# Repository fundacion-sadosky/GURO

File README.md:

🌐 [English](README.en.md)

# GURO

**Kit de conversión para robots Robobloq Qoopers con [BBC Micro:bit](https://www.microbit.org)**

La Fundación Sadosky desarrolla el kit GURO para actualizar los robots Robobloq Qoopers —ya desplegados en escuelas de todo el país— reemplazando el controlador propietario Qmind Plus por la [BBC Micro:bit](https://www.microbit.org): una placa didáctica de hardware y software completamente abiertos, con una comunidad global activa de millones de docentes y estudiantes.

---

## ¿Qué es el kit GURO?

El kit GURO consiste en una **placa adaptadora** (diseño KiCad incluido en este repositorio) y un **gabinete** que permiten montar una BBC Micro:bit y una placa expansora [Kittenbot Robotbit](https://kittenbothk-eng.readthedocs.io/en/latest/Microbit_eboard/Robotbit/robotbitMC.html) en el chasis del Robobloq Qoopers, conectando los motores y sensores existentes del robot.

El resultado es un robot funcional, programable desde el navegador en bloques visuales o en Python, sin depender de ningún software propietario ni de un único proveedor.

El modelos 3D del robot y el gabinete están disponibles en este repositorio y en [Tinkercad](https://www.tinkercad.com/things/2tzfirybpMV-guro-microrbit-para-robolboq-qoopers-260401)

---

## Requisitos

- **Kit Robobloq Qoopers** — chasis, motores, sensores y partes mecánicas (sin el Qmind Plus)
- **Kit GURO** — placa adaptadora y gabinete Micro:bit (este repositorio)
- **[BBC Micro:bit](https://www.microbit.org)** v1 o v2
- Un destornillador Phillips
- Una computadora con puerto USB

---

## Guía de armado

La documentación completa está publicada en:

**[guro.readthedocs.io](https://guro.readthedocs.io/)**

Incluye el inventario de piezas, 16 pasos ilustrados y las instrucciones de programación. También disponible [en PDF](docs/user-guide_2026-04-01.pdf)

---

## Programación del robot

Una vez armado el GURO, cargá un programa a la Micro:bit desde el navegador, sin instalar nada:

### Opción 1 — Bloques visuales (MakeCode)

Usá el editor [Microsoft MakeCode](https://makecode.microbit.org) con la extensión **Kittenbot Robotbit** para programar el robot con bloques. [Ver instrucciones de la extensión.](https://kittenbothk-eng.readthedocs.io/en/latest/Microbit_eboard/Robotbit/robotbitMC.html)

### Opción 2 — Python

Usá el [editor oficial de MicroPython](https://python.microbit.org/v/3) de la [Micro:bit Educational Foundation](https://github.com/microbit-foundation).

El framework [**microbitML**](https://github.com/fundacion-sadosky/microbitML) (Fundación Sadosky) incluye la actividad `mbGURO`, lista para comandar al robot. Podés descargar el archivo `.hex` y bajarlo directamente a la placa.

---

## Estructura del repositorio

```
docs/               Documentación del sitio (properDocs + Obsidian)
kit GURO/           Inventario del kit 
gabinete/           Gabinete para Micro:bit y placa expansora
placa adaptadora/   Diseño de la placa PCB adaptadora (KiCad)
scripts/            Scripts de generación de documentación (properDocs/MkDocs)
mkdocs.yml          Configuración del sitio de documentación 
docs-requirements.txt  Dependencias Python para compilar la documentación 
```

La carpeta `docs/` está configurada como un vault de [Obsidian](https://obsidian.md), lo que permite editarla sin usar la terminal. Ver [Contribuciones para redactores](https://guro.readthedocs.io/contributing/for-writers/).

---

## Oportunidades de colaboración

Estas son algunas tareas concretas en las que podés contribuir al proyecto:

1. **Avistaje**: si lo usan en tu escuela, compartí la experiencia B)
1. **Completar la Mecánica**: pasar el diseño 3D del gabinete de [Tinkercad](https://www.tinkercad.com/things/2tzfirybpMV-guro-microrbit-para-robolboq-qoopers-260401) a un formato mantenible/paramétrico como openScad.
1. **Completar la Mecánica**: el capó no encaja en la tapa del gabinete.
1. **Completar la Mecánica**: la tapa del gabinete choca con el porta batería del Kittenbot.
1. **Completar la Guía**: los pasos 13, 14 y 16 de la guía de armado no tienen imágenes aún. Si tenés un kit armado, podés tomar las fotos y abrir un PR.
1. **Traducir la documentación al Inglés**: la guía de armado y el README están disponibles solo en español. Traducirlos ampliaría el alcance del proyecto a la comunidad internacional de Micro:bit.
1. **Crear una extensión de MakeCode específica para GURO**: actualmente se usa la extensión genérica de Kittenbot Robotbit. Una extensión propia simplificaría la programación en bloques con nombres y funciones adaptados al GURO.

## Contribuciones

Las contribuciones son bienvenidas, independientemente del perfil técnico.

- **Redactores y docentes**: editá la documentación con [Obsidian](https://obsidian.md) abriendo la carpeta `docs/` como vault. Ver [guía para redactores](https://guro.readthedocs.io/contributing/for-writers/).
- **Desarrolladores**: mirá la [guía para desarrolladores](https://guro.readthedocs.io/contributing/for-developers/).
- **Errores o sugerencias**: abrí un [issue](../../issues) en este repositorio.

---

## Créditos

Colaboradores/as iniciales, por orden alfabético:

| Nombre   | Rol                         |
|---------------------------|-----------------------------|
| Alarcón Lasagno, Ramiro   | Doc, SW, HW                 | 
| Batlle, Leandro           | Doc, SW , HW, idea original |
| Gentile Montes, Ezequiel  | Mecánica                    |
| Medel, Ricardo            | Licencias Doc, FLOSS, OSHW  |

*¿Contribuiste al proyecto? Abrí un PR para agregar tu nombre y aportes.*

Este proyecto utiliza la [BBC Micro:bit](https://www.microbit.org), desarrollada por la [Micro:bit Educational Foundation](https://github.com/microbit-foundation). La Micro:bit Foundation publica sus especificaciones de hardware, firmware y recursos educativos bajo licencias abiertas en [github.com/microbit-foundation](https://github.com/microbit-foundation).

---

## Marcas registradas

Los nombres de productos y marcas mencionados en este repositorio (incluyendo BBC Micro:bit, Robobloq, Qoopers, Kittenbot, Robotbit, Microsoft MakeCode, entre otros) son propiedad de sus respectivos titulares y se utilizan únicamente con fines identificativos y descriptivos.

## Naturaleza del proyecto

El desarrollo comenzó en la Fundación Sadosky en el marco del Programa para el Desarrollo de la Infraestructura destinada a Promover la Capacidad Emprendedora financiado por la [CAF | Banco de desarrollo de América Latina y El Caribe](https://www.caf.com/).  GURO es un kit de conversión que permite reutilizar las partes mecánicas, motores y sensores del Robobloq Qoopers con una nueva  placa controladora. El proyecto no modifica ni redistribuye el firmware, software ni diseños de hardware de los productos de terceros que integra. 

## Garantías y responsabilidad

Este proyecto se distribuye sin garantía de ningún tipo, expresa o  implícita. El armado, uso y eventual modificación del kit son responsabilidad exclusiva del usuario. Consultá las licencias GPLv3 y CC BY-SA 4.0 incluidas en este repositorio para los términos  completos. El uso del kit en entornos educativos debe realizarse bajo supervisión docente y conforme a las normativas de seguridad aplicables en cada jurisdicción. 

## Licencias

El proyecto se distribuye bajo una **licencia dual**:

### Código y diseños de hardware
Publicado bajo la [**GNU General Public License v3.0**](LICENSE) (GPLv3).
Podés usar, modificar y redistribuir el código y los diseños KiCad, siempre que cualquier obra derivada se publique bajo la misma licencia.

### Documentación
Publicada bajo [**Creative Commons Atribución-CompartirIgual 4.0 Internacional**](https://creativecommons.org/licenses/by-sa/4.0/) (CC BY-SA 4.0).
Podés copiar, adaptar y redistribuir el contenido —incluso con fines comerciales— siempre que des crédito a los autores originales y distribuyas las obras derivadas bajo la misma licencia.

---

<p align="center">
  <a href="https://www.fundacionsadosky.org.ar">Fundación Sadosky</a>
</p>

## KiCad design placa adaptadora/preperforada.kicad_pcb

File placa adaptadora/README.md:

🌐 [English](README.en.md)

# Placa Adaptadora — Kit GURO

Diseño [KiCad](https://www.kicad.org/) de la **placa adaptadora**, componente del [kit GURO](../kit%20GURO/README.md).

---

## ¿Qué hace esta placa?

La placa adaptadora es el puente eléctrico central del kit GURO.
Conecta todos los periféricos del chasis Qoopers a la [Kittenbot Robotbit](https://kittenbothk-eng.readthedocs.io/en/latest/Microbit_eboard/Robotbit/robotbitMC.html):

```
Kittenbot Robotbit
      │
      ├── Motores (×2) — conectores de 6 pines
      ├── Sensores  ─┐
      ├── GPIO       ├── conectores RJ25 (6 Posiciones / 6 Contactos)
      └── Panel LED ─┘
```

También incorpora la conexión a la **placa de alimentación** del kit, PRECAUCIÓN:

> [!WARNING]
> NUNCA conectar la batería del Robobloq Qoopers directamente al Kittenbot Robotbit: es necesario regular su tensión a 5V (con 15W), que es la función de la "placa de alimentación".

---

## Vista del diseño PCB

El diseño está optimizado para ser **intercambiable con una [placa universal de 50×70 mm](https://www.printables.com/model/797008-perfboard-50x70mm-18-x-24-holes)**, lo que permite replicarla sin acceso a fabricación de PCB profesional.

---

## Opciones de fabricación o reemplazo

| Opción | Dificultad | Resultado |
|--------|-----------|-----------|
| **A** — Fabricar con los archivos KiCad | Media — requiere enviar Gerbers a un fabricante | PCB profesional, reproducible |
| **B** — Placa universal 50×70 mm | Media — requiere soldadura | Resultado equivalente, sin fabricante externo |
| **C** — Conexión directa sin PCB | Baja — cables y dupont | Funcional, menos prolijo |

Cualquiera sea la opción elegida, el resultado eléctrico es equivalente.

---

## Opción A — Fabricar con los archivos KiCad

Los archivos de esta carpeta son un proyecto de [KiCad](https://www.kicad.org/) (software libre de diseño de PCB).

**Para fabricar:**
1. Abrí el proyecto en KiCad y exportá los **archivos Gerber** (Archivo → Fabricar → Gerbers)
2. Subí los Gerbers a cualquier servicio de fabricación de PCB (JLCPCB, PCBWay, Aisler, etc.)
3. Pedido típico: 5 unidades, 2 capas, FR4, 1.6 mm de espesor

**Para editar el diseño**, necesitás [KiCad 7 o superior](https://www.kicad.org/download/).

---

## Opción B — Placa universal 50×70 mm

### Componentes necesarios para soldar

| Componente | Cantidad | Notas |
|---|---|---|
| Placa universal perforada 50×70 mm | 1 | Paso de 2.54 mm |
| Conector RJ25 hembra (6P6C) | 5 | Para sensores y panel LED |
| Conector 2 pines macho (paso 2.54 mm) | 2 | Para motores |
| Pin header hembra 40 pines (paso 2.54 mm) | 2 | Para Kittenbot Robotbit |
| Cable de conexión (wire wrap o similar) | — | Para puentes entre pads |

### Procedimiento general

1. Posicioná los conectores RJ25 siguiendo el layout del PCB como referencia
2. Soldá los conectores y trazá los puentes según el esquemático KiCad
3. Verificá continuidad con multímetro antes de conectar

---

## Opción C — Conexión directa sin PCB

Si no disponés de soldador ni fabricante, es posible conectar directamente los periféricos a la Kittenbot Robotbit con **cables dupont**, sin PCB intermedio.

Consultá el [paso 13 (motores)](../docs/user-guide/index.md) y el [paso 14 (sensores)](../docs/user-guide/index.md) de la guía de armado para el detalle de cada conexión.

---

## Precauciones y Licencia

Aplican todas las licencias y precauciones de seguridad y salud citadas en el [apartado legal del repositorio principal](../README.md#garantías-y-responsabilidad), especialmente al realizar soldadura y manipulación de herramientas eléctricas.

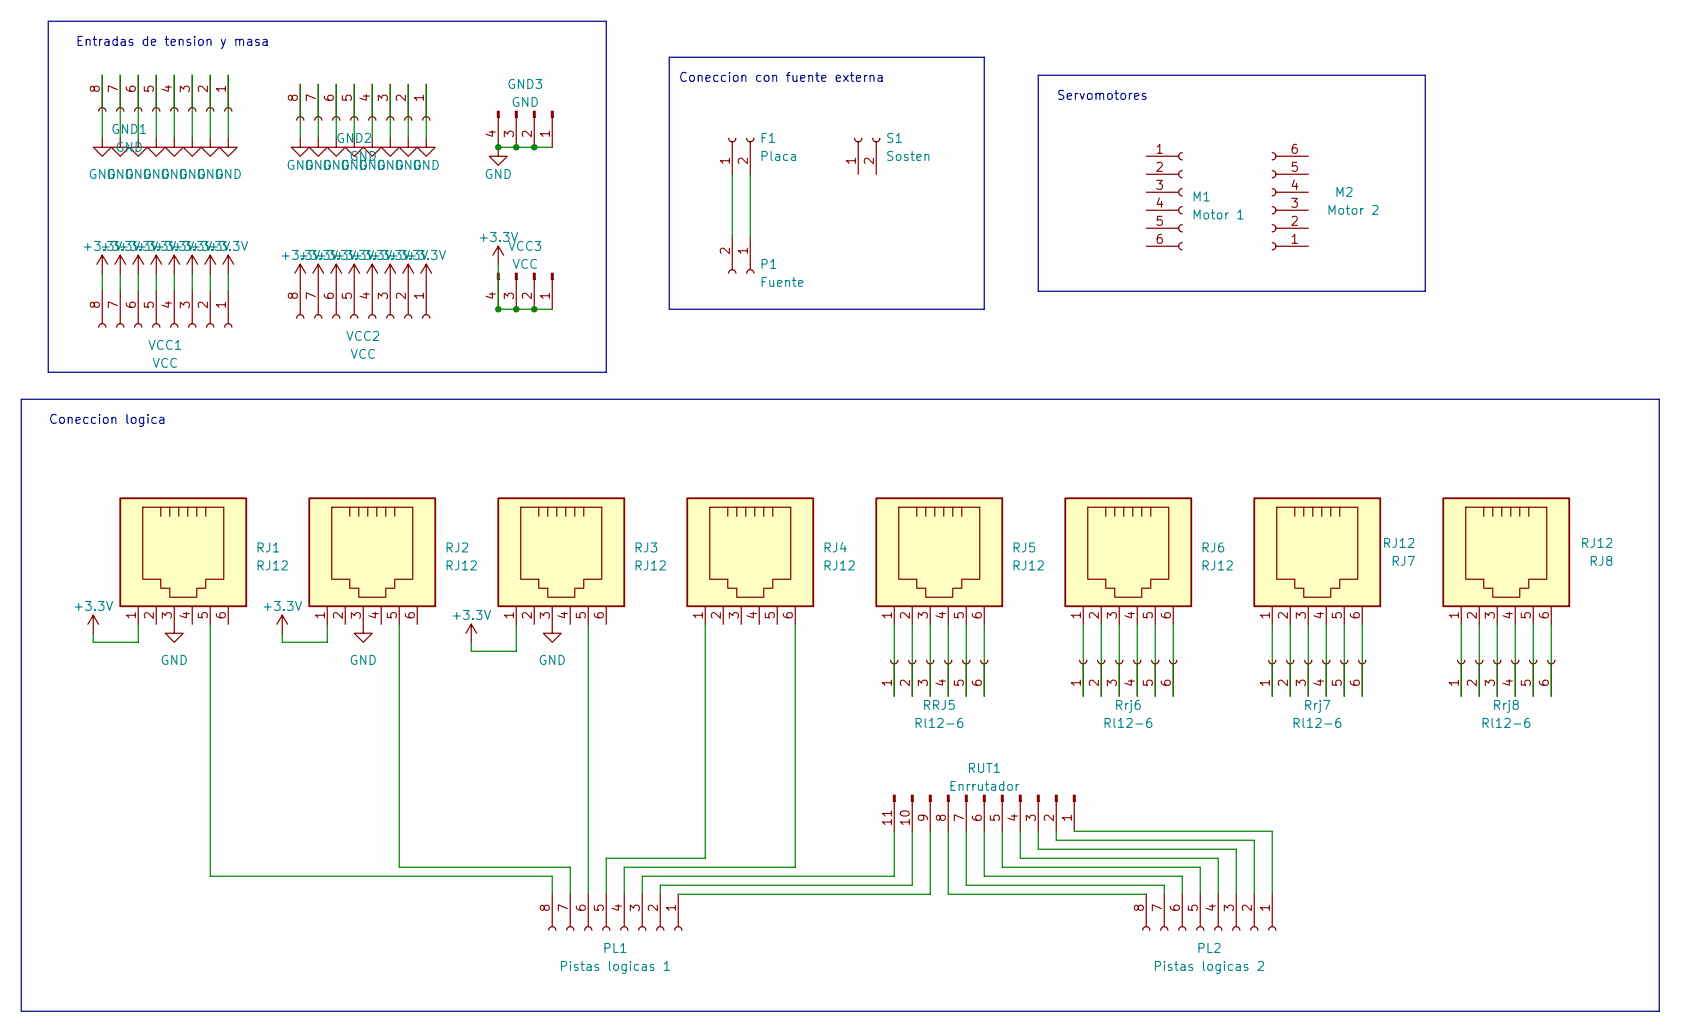
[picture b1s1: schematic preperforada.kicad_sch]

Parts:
F1: Placa; PinSocket_1x02_P2.54mm_Vertical
GND1, GND2: GND; PinSocket_1x08_P2.54mm_Vertical
GND3: GND; PinHeader_1x04_P2.54mm_Vertical
M1: Motor 1; PinSocket_1x06_P2.54mm_Vertical
M2: Motor 2; PinSocket_1x06_P2.54mm_Vertical
P1: Fuente; PinSocket_1x02_P2.54mm_Vertical
PL1: Pistas logicas 1; PinSocket_1x08_P2.54mm_Vertical
PL2: Pistas logicas 2; PinSocket_1x08_P2.54mm_Vertical
RJ1, RJ2, RJ3, RJ4, RJ5, RJ6, RJ7, RJ8: RJ12; RJ12_Amphenol_54601
RRJ5: Rl12-6; PinHeader_1x06_P2.54mm_Vertical
RUT1: Enrrutador; PinHeader_1x11_P2.54mm_Vertical
Rrj6, Rrj7, Rrj8: Rl12-6; PinHeader_1x06_P2.54mm_Vertical
S1: Sosten; PinSocket_1x02_P2.54mm_Vertical
VCC1, VCC2: VCC; PinSocket_1x08_P2.54mm_Vertical
VCC3: VCC; PinHeader_1x04_P2.54mm_Vertical

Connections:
+3.3V: RJ1.1, RJ2.1, RJ3.1, VCC1.1, VCC1.2, VCC1.3, VCC1.4, VCC1.5, VCC1.6, VCC1.7, VCC1.8, VCC2.1, VCC2.2, VCC2.3, VCC2.4, VCC2.5, VCC2.6, VCC2.7, VCC2.8, VCC3.1, VCC3.2, VCC3.3, VCC3.4
GND: GND1.1, GND1.2, GND1.3, GND1.4, GND1.5, GND1.6, GND1.7, GND1.8, GND2.1, GND2.2, GND2.3, GND2.4, GND2.5, GND2.6, GND2.7, GND2.8, GND3.1, GND3.2, GND3.3, GND3.4, RJ1.3, RJ2.3, RJ3.3
unnamed: F1.1, P1.2
unnamed: F1.2, P1.1
unnamed: PL1.1, RUT1.9
unnamed: PL1.2, RUT1.10
unnamed: PL1.3, RUT1.11
unnamed: PL1.4, RJ4.6
unnamed: PL1.5, RJ4.1
unnamed: PL1.6, RJ3.5
unnamed: PL1.7, RJ2.5
unnamed: PL1.8, RJ1.5
unnamed: PL2.1, RUT1.1
unnamed: PL2.2, RUT1.2
unnamed: PL2.3, RUT1.3
unnamed: PL2.4, RUT1.4
unnamed: PL2.5, RUT1.5
unnamed: PL2.6, RUT1.6
unnamed: PL2.7, RUT1.7
unnamed: PL2.8, RUT1.8
unnamed: RJ5.1, RRJ5.1
unnamed: RJ5.2, RRJ5.2
unnamed: RJ5.3, RRJ5.3
unnamed: RJ5.4, RRJ5.4
unnamed: RJ5.5, RRJ5.5
unnamed: RJ5.6, RRJ5.6
unnamed: RJ6.1, Rrj6.1
unnamed: RJ6.2, Rrj6.2
unnamed: RJ6.3, Rrj6.3
unnamed: RJ6.4, Rrj6.4
unnamed: RJ6.5, Rrj6.5
unnamed: RJ6.6, Rrj6.6
unnamed: RJ7.1, Rrj7.1
unnamed: RJ7.2, Rrj7.2
unnamed: RJ7.3, Rrj7.3
unnamed: RJ7.4, Rrj7.4
unnamed: RJ7.5, Rrj7.5
unnamed: RJ7.6, Rrj7.6
unnamed: RJ8.1, Rrj8.1
unnamed: RJ8.2, Rrj8.2
unnamed: RJ8.3, Rrj8.3
unnamed: RJ8.4, Rrj8.4
unnamed: RJ8.5, Rrj8.5
unnamed: RJ8.6, Rrj8.6

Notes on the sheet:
Entradas de tension y masa
Coneccion con fuente externa
Coneccion logica
Servomotores

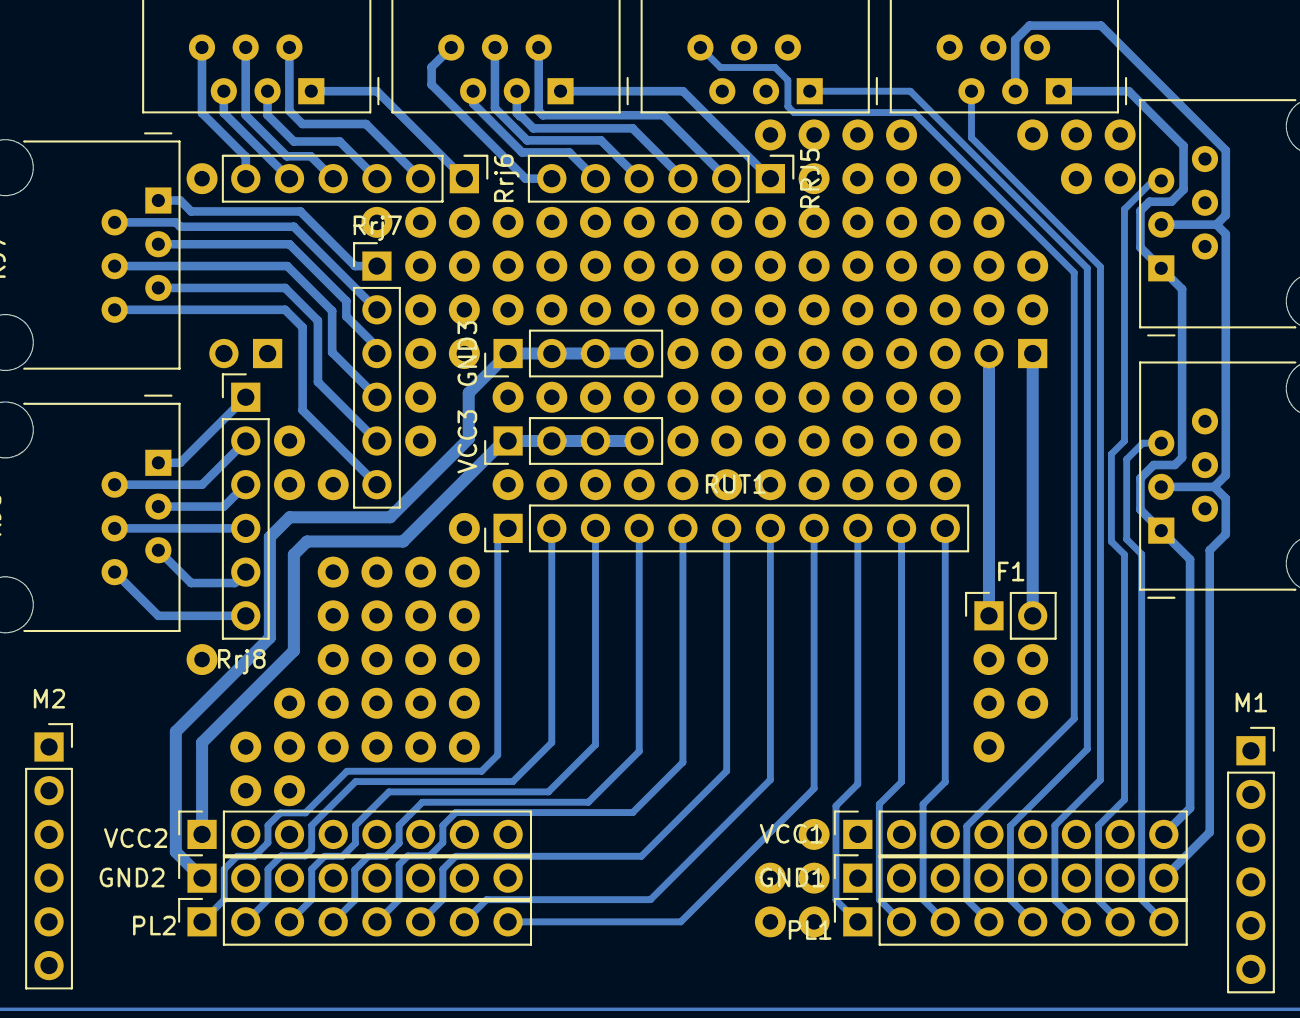
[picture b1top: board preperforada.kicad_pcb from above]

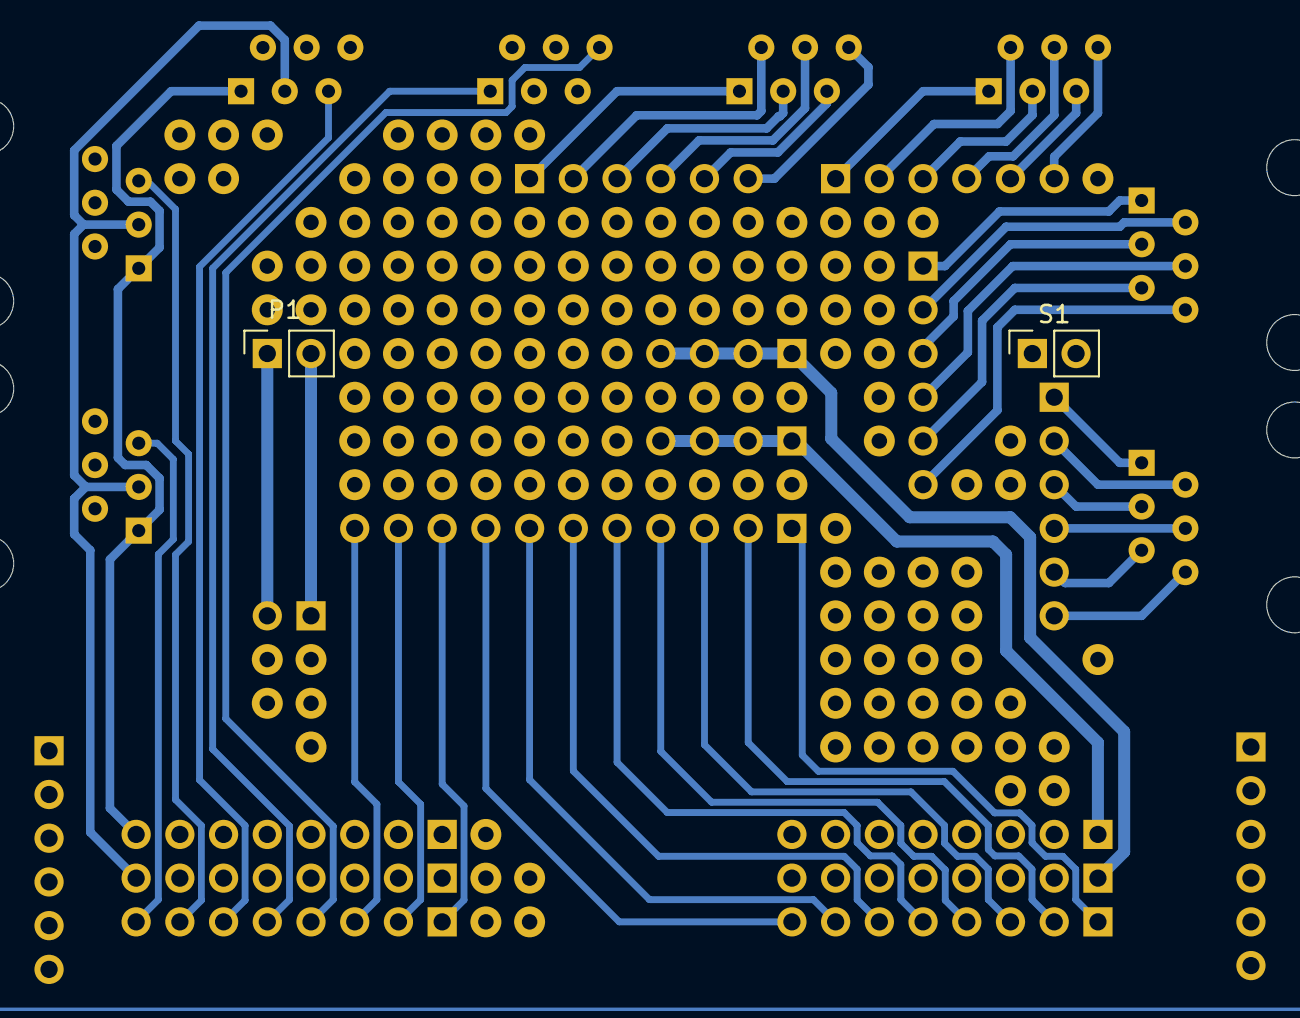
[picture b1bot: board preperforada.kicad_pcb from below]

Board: 2 copper layers, 26 parts (2 on the bottom side), 44 nets.

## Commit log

2026-04-02 inicial (cierre de 2.4.2.3)
2026-04-02 guro.readthedocs.io
2026-04-03 docs
2026-04-06 English auto-translation from the Spanish original
2026-04-09 instrucciones de fabricación
